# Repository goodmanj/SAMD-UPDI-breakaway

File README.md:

# SAMD-UPDI-breakaway
 A USB-to-UART-to-UPDI circuit board designed in KiCAD, based on Quentin Bolsee's [SAMD11C14 UART/UPDI programmer](https://fabacademy.org/2020/labs/ulb/students/quentin-bolsee/projects/samd11c_uart-updi/).  This version is designed so you can snap it in half to create a USB-to-UART adapter, and a UART-to-UPDI adapter, that can be used separately or joined together.  If you don't plan to use the "breakaway" feature, you don't need to solder in the 6-pin headers, and you might want to delete the internal slot to make it stronger.

* [Detailed assembly instructions](https://docs.google.com/document/d/1IBKZu-5q0hexmYGWNFWA64giY4mmglZQRK6Q2b19Nos/)
* [Quentin Bolsee's "SAMD11C_Serial" Arduino sketch](https://github.com/qbolsee/SAMD11C_serial): firmware for this board
* [Fab SAM Core for Arduino](https://github.com/qbolsee/ArduinoCore-fab-sam): Arduino core needed for Quentin's sketch

## USB Port Backplate
You may find that the USB port is a little too skinny to fit nicely into some USB ports.  You can 3-d print a [Back Plate](BackPlate.stl) and glue or double-sided-tape it to the board to make it fit better.

 # Parts List
* [MCP1700T-3302E/TT LDO Voltage Regulator 5v->3.3v](https://www.mouser.com/ProductDetail/579-MCP1700T3302E-TT)
* [ATSAMD11C14A-SSNT SAMD microcontroller](https://www.mouser.com/ProductDetail/556-ATSAMD11C14ASSNT)
* [M20-8750242 2.54mm 2+2 DIL SMT header](https://www.mouser.com/ProductDetail/855-M20-8750242)
* [M20-8890645 2.54mm 6 way horzontal male SMT header](https://www.mouser.com/ProductDetail/855-M20-8890645)
* [M20-7910642R 2.54mm 6 way horzontal female SMT header](https://www.mouser.com/ProductDetail/855-M20-7910642R)  Qty: 2
* [1206 SMD resistor 4.7k](https://www.mouser.com/ProductDetail/652-CR1206-JW-472ELF)
* [1206 SMD resistor 1.2k](https://www.mouser.com/ProductDetail/652-CR1206FX-1201ELF)
* [1206 SMD zero-ohm SMD jumper](https://www.mouser.com/ProductDetail/652-CR1206-J-000ELF)
* [1206 SMD 1uF ceramic capacitors](https://www.mouser.com/ProductDetail/187-CL31B105KAHNFNE) Qty: 2

# Blinky Version
There is also a [version of this board with LED lights](Blinky-version/) to indicate serial data activity.  You will need two additional 1206 1.2k resistors, and two 1206 1.2k LEDs.

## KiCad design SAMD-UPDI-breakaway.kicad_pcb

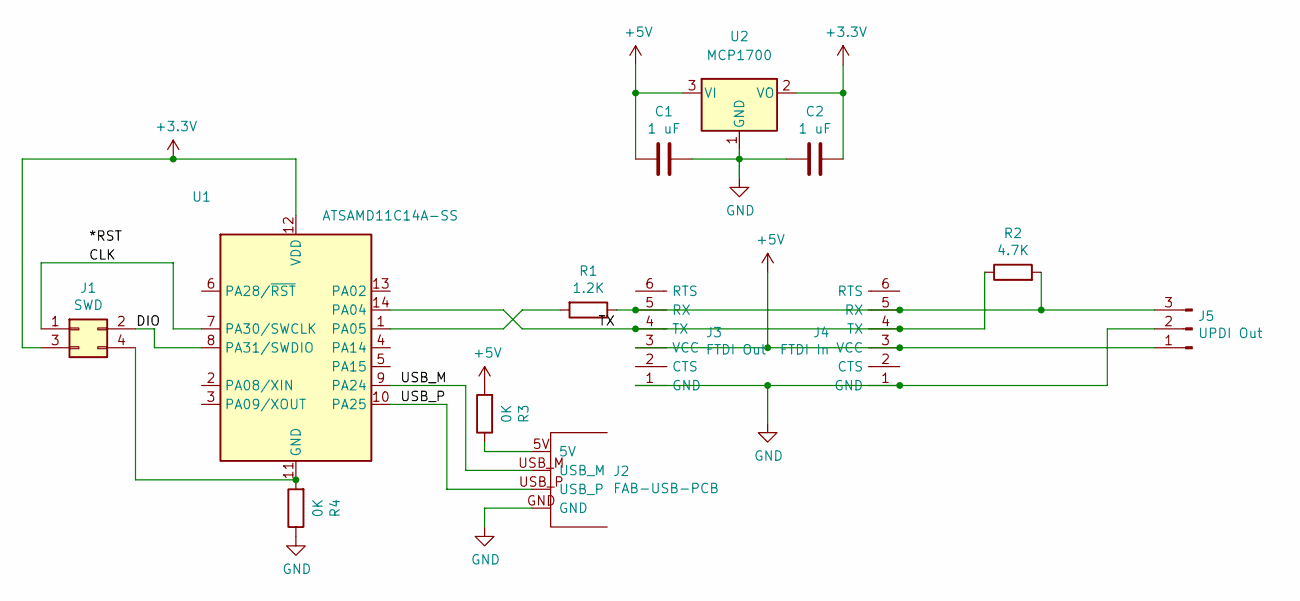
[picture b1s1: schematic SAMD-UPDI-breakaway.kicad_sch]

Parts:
C1, C2: 1 uF; C_1206
J1: SWD; PinHeader_2x02_P2.54mm_Vertical_SMD
J2: FAB-USB-PCB; FAB_USB-A-PCB
J3: FTDI Out; PinHeader_FTDI_01x06_P2.54mm_Horizontal_SMD
J4: FTDI In; PinHeader_FTDI_01x06_P2.54mm_Horizontal_SMD
J5: UPDI Out; PinHeader_1x03_P2.54mm_Horizontal_SMD
R1: 1.2K; R_1206
R2: 4.7K; R_1206
R3, R4: 0K; R_1206
U1: ATSAMD11C14A-SS; SOIC-14_3.9x8.7mm_P1.27mm
U2: MCP1700; SOT-23

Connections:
+3V3: C2.1, J1.3, U1.12 (VDD), U2.2 (VO)
+5V: C1.2, J3.3 (VCC), J4.3 (VCC), J5.1, R3.2, U2.3 (VI)
/CLK: J1.1, U1.7 (PA30/SWCLK)
/DIO: J1.2, U1.8 (PA31/SWDIO)
/TX: J3.4 (TX), J4.4 (TX), R2.1, U1.14 (PA04)
/USB_M: J2.USB_M, U1.9 (PA24)
/USB_P: J2.USB_P, U1.10 (PA25)
GND: C1.1, C2.2, J2.GND, J3.1 (GND), J4.1 (GND), J5.2, R4.1, U2.1 (GND)
unnamed: J1.4, R4.2, U1.11 (GND)
unnamed: J2.5V, R3.1
unnamed: J3.5 (RX), J4.5 (RX), J5.3, R1.1, R2.2
unnamed: R1.2, U1.1 (PA05)

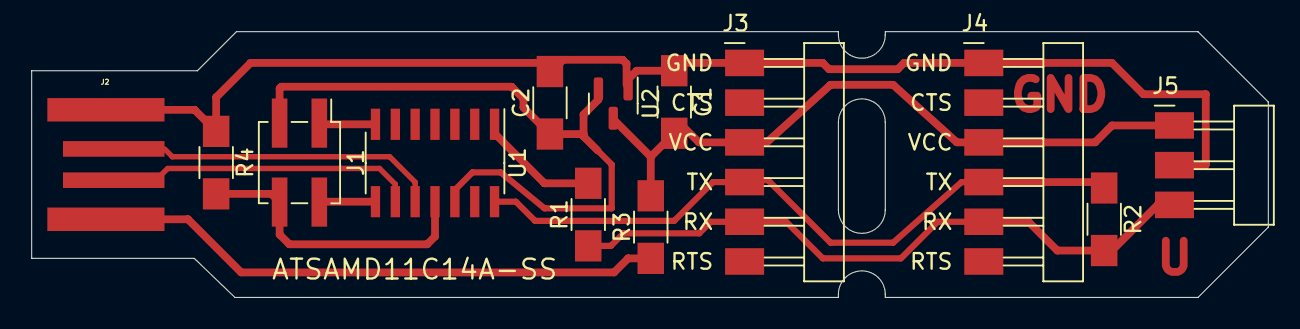
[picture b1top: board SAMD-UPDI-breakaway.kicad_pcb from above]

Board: 2 copper layers, 79.1 x 17.0 mm, 13 parts (0 on the bottom side), 12 nets.

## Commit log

2022-01-20 First draft, repo creation.
    Board hasn't been programmed or tested yet!
2022-02-14 Outline and Trace files added
2022-02-14 Removed extraneous files
2022-02-14 Removed mill script file
2022-02-14 Added backplate STL
2022-02-16 Replace RST on JTAG header with Vref. Labels
    ATMEL Ice programmer doesn't use RST, but requires that the target microcontroller's VCC be provided for it to sense. Remove RST from JTAG header, provide VCC instead.
2022-02-16 Alternate version with LEDs to indicate serial activity
2022-02-16 Create README.md for BLinkenlights
2022-02-16 Update Readme.md with links to instructions
2022-02-16 Update Readme.md to talk about blinkenlights
2022-02-17 Smaller USB outline
2022-02-18 Adjust USB size
2022-02-18 Updated Blinkenlights readme
2022-02-18 Edit README to talk about backplate
2022-02-18 Typo in Blinkenlights readme
2022-02-18 Make prettier component layout images
2022-02-18 Reverting USB size changes
2022-02-18 Update outline.svg with reverted USB size change
2022-02-18 Adjust slot size
2022-02-18 Name change
2022-02-18 Tweak backplate design.
    BackPlate-small is for earlier USB designs.
